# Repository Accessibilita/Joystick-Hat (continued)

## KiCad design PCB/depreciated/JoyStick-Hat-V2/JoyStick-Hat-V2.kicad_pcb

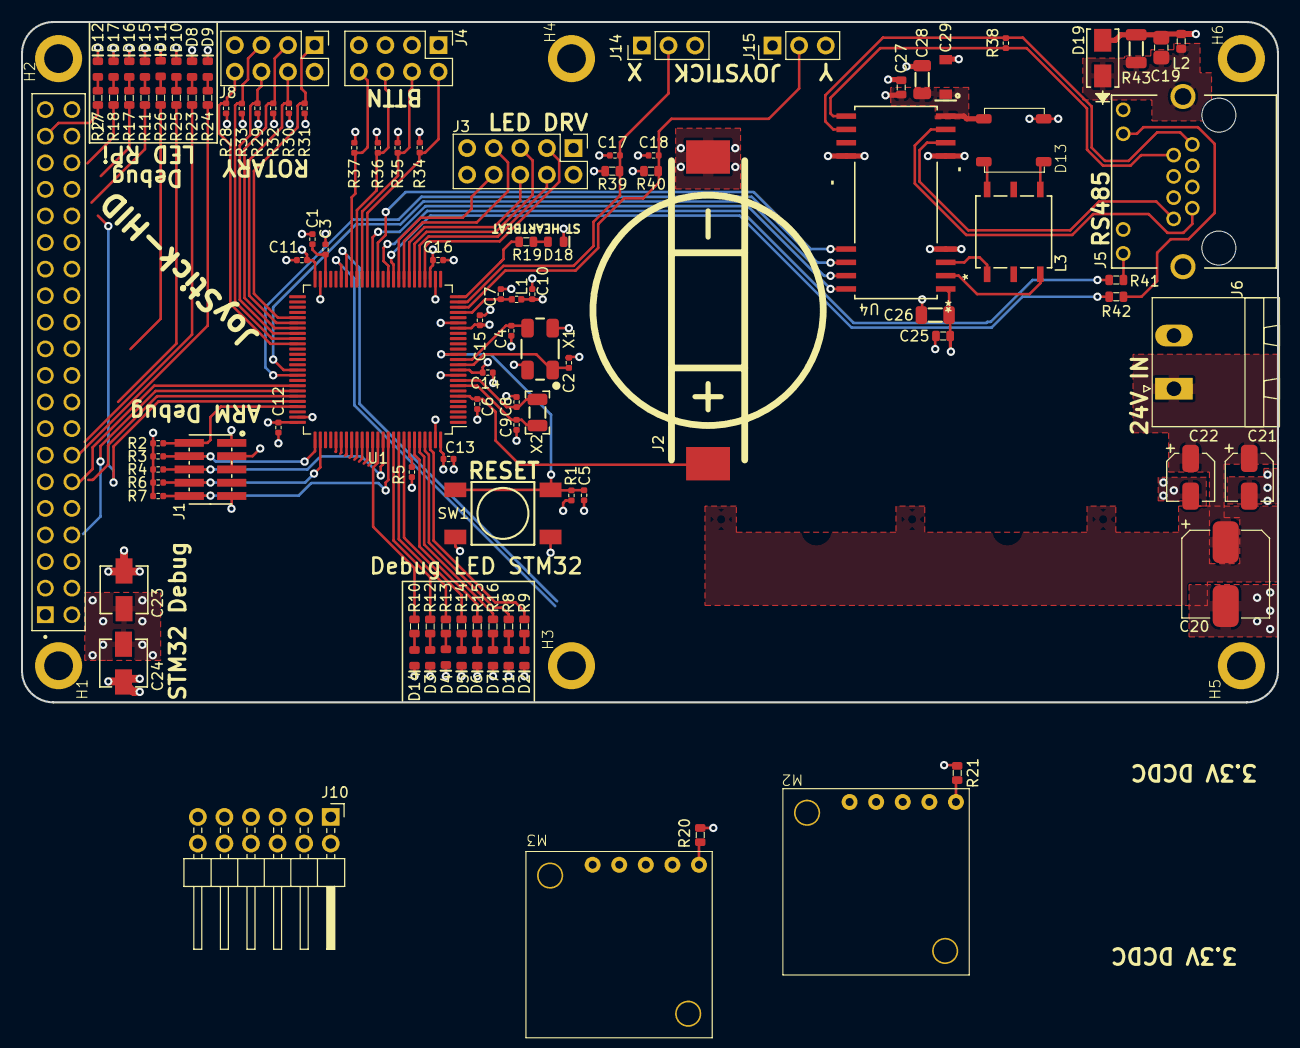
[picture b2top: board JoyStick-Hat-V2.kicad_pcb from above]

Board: 4 copper layers, 120.0 x 65.0 mm, 117 parts (0 on the bottom side), 104 nets.

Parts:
C1, C5, C6, C7, C10, C11, C12, C13, C14, C15, C16, C17, C18: C0402C104K9PACTU; R0402
C2, C4: GCM1555C1H180GA16D; C0402
C3: GRM155R60J475ME47D; C0402
C8, C9: CL05C090CB5NNNC; C0402
C19: C0805C103KCRACAUTO; C0805
C20: UUQ1H470MCL1GS; CP_Elec_8x10
C21: UUQ1H100MCL1GB; CP_Elec_4x5.3
C22: UUQ1H010MCL1GB; CP_Elec_4x5.3
C23, C24: UCM1C470MCL1GS
C25, C27: CL10B104JB8NNNC; C0603
C26, C28: CGA5L3X5R1V106K160AB; C1206
C29: C1206C105K3RACAUTO; D_SOD-123
D1, D2, D3, D4, D5, D6, D7, D14, D18: LTST-C194TBKT; LED0603
D8, D9, D10, D11, D12, D15, D16, D17: LTST-C194KGKT; LED0603
D13: LMB110S-TP
D19: SMAJ30CA
H1, H2, H3, H4, H5, H6: MountingHole_Pad; RPI_HAT_HOLE
J1: 20021121-00010C4LF
J2: BU2032SM-JJ-GTR
J3: Conn_02x05_Odd_Even; PinHeader_2x05_P2.54mm_Vertical
J4, J8: Conn_02x04_Odd_Even; PinHeader_2x04_P2.54mm_Vertical
J5: RJHSE-5381; AMPHENOL_RJHSE-5381
J6: 1757242; PhoenixContact_MSTBA-G_02x5.08mm_Angled
J7: Raspberry_Pi_2_3; SULLINS_PPPC202LFBN-RC_RPi5
J10: Conn_02x06_Odd_Even; PinHeader_2x06_P2.54mm_Horizontal
J14, J15: Conn_01x03_Pin; PinHeader_1x03_P2.54mm_Vertical
L1: BLM15HG601SN1D
L2: MI0603K300R-10
L3: Q4470-CL; SO6_Q4470-CL_C-SIZE_COC
M2: D24V22F5; D24V22F12
M3: D24V22F3; D24V22F12
R1, R2, R3, R4, R6, R7: RC0402FR-071KL; R0402
R5: RC0402FR-0710KL; R0402
R8, R9, R10, R11, R12, R13, R14, R15, R16, R17, R18, R19, R23, R24, R25, R26, R27, R41, R42: RC0603FR-07470RL; R0603
R20, R21: RC0603FR-072K2L; R0603
R28, R29, R30, R31, R32, R33, R34, R35, R36, R37: RC0402FR-072K2L; R0402
R38: AC0402FR-07120RL; R0402
R39, R40: RT0603BRD071ML; R0603
R43: RC1206FR-071ML; R1206
SW1: TL3301NF260QG
U1: STM32F446VETx; LQFP-100_14x14mm_P0.5mm
U4: MAX3535ECWI+T; 21-0145_W28M&plus_9_MXM
X1: ABM3B-8.000MHZ-B2-T; ABM3B8.000MHZB2T
X2: ABS07-32.768KHZ-9-T

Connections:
+3.3V: C10.1, C11.1, C12.1, C13.1, C14.1, C15.1, C16.1, C25.2, C26.2, J1.1, J3.1, J3.2, J14.3, J15.3, L1.1, M3.5 (VOUT), R1.1, R2.1, R3.1, R4.1, R6.1, R7.1, R20.2, R21.2, R28.2, R29.2, R30.2, R31.2, R32.2, R33.2, R34.2, R35.2, R36.2, R37.2, R39.2, R40.2, U1.11 (VDD), U1.19 (VDD), U1.28 (VDD), U1.50 (VDD), U1.75 (VDD), U1.100 (VDD), U4.1 (VCC1)
+5V: C23.1, C24.1, C27.2, C28.2, C29.2, D13.3, J7.2 (5V), J7.4 (5V), M2.5 (VOUT), U4.14 (VCC2)
+24V: C20.1, C21.1, C22.1, J6.1, M2.3 (VIN), M3.3 (VIN)
/JoyStick Interface/BUTTON1: J4.2, R34.1, U1.40 (PE9)
/JoyStick Interface/BUTTON2: J4.4, R35.1, U1.41 (PE10)
/JoyStick Interface/BUTTON3: J4.6, R36.1, U1.42 (PE11)
/JoyStick Interface/BUTTON4: J4.8, R37.1, U1.43 (PE12)
/JoyStick Interface/JOYSTICK_X: C17.1, J14.2, R39.1, U1.24 (PA1)
/JoyStick Interface/JOYSTICK_Y: C18.1, J15.2, R40.1, U1.23 (PA0)
/JoyStick Interface/ROTARY1_POLE1: J8.1, R31.1, U1.55 (PD8)
/JoyStick Interface/ROTARY1_POLE2: J8.3, R32.1, U1.57 (PD10)
/JoyStick Interface/ROTARY1_POLE3: J8.5, R33.1, U1.59 (PD12)
/JoyStick Interface/ROTARY2_POLE1: J8.8, R28.1, U1.60 (PD13)
/JoyStick Interface/ROTARY2_POLE2: J8.6, R29.1, U1.58 (PD11)
/JoyStick Interface/ROTARY2_POLE3: J8.4, R30.1, U1.56 (PD9)
/Power/3.3V_PG: M3.1 (PG), R20.1, U1.44 (PE13)
/Power/5V_PG: M2.1 (PG), R21.1, U1.45 (PE14)
/RPi_Interface/RPI_ST_UART_CTS: J7.36 (GPIO16), U1.71 (PA12)
/RPi_Interface/RPI_ST_UART_RTS: J7.11 (GPIO17), U1.70 (PA11)
/RPi_Interface/RPI_ST_UART_RX: J7.10 (GPIO15/RXD), U1.68 (PA9)
/RPi_Interface/RPI_ST_UART_TX: J7.8 (GPIO14/TXD), U1.69 (PA10)
/RS485 To Motor Controller Interface/A_RS485: J5.1, R38.1, U4.16 (A)
/RS485 To Motor Controller Interface/B_RS485: J5.2, R38.2, U4.15 (B)
/RS485 To Motor Controller Interface/RJ45_SHIELD: C19.1, D19.1, J5.S1, J5.S2, L2.1, R43.2
/RS485 To Motor Controller Interface/RS485_RXD: U1.39 (PE8), U4.28 (RO1)
/RS485 To Motor Controller Interface/RS485_RX_EN: U1.66 (PC9), U4.26 (DE)
/RS485 To Motor Controller Interface/RS485_RX_LED: R42.2, U1.35 (PB0)
/RS485 To Motor Controller Interface/RS485_TXD: U1.38 (PE7), U4.25 (DI)
/RS485 To Motor Controller Interface/RS485_TX_EN: U1.65 (PC8), U4.27 (RE)
/RS485 To Motor Controller Interface/RS485_TX_LED: R41.2, U1.36 (PB1)
/RS485 To Motor Controller Interface/Y_RS485: J5.7, U4.13 (Y)
/RS485 To Motor Controller Interface/Z_RS485: J5.8, U4.12 (Z)
/STM32F446RET6-MCU/LED_DRIVER_BLANK: J3.7, U1.33 (PC4)
/STM32F446RET6-MCU/LED_DRIVER_BLANK2: J3.5, U1.31 (PA6)
/STM32F446RET6-MCU/LED_DRIVER_MOSI: J3.6, U1.32 (PA7)
/STM32F446RET6-MCU/LED_DRIVER_SCLK: J3.4, U1.30 (PA5)
/STM32F446RET6-MCU/LED_DRIVER_XLAT: J3.3, U1.29 (PA4)
/STM32F446RET6-MCU/LED_DRIVER_XLAT2: J3.8, U1.34 (PC5)
/STM32F446RET6-MCU/NJTRST: J1.10, R7.2, U1.90 (PB4)
/STM32F446RET6-MCU/NRST: C5.1, R1.2, SW1.1, SW1.2, U1.14 (NRST)
/STM32F446RET6-MCU/OSC32_IN: C9.2, U1.8 (PC14), X2.2
/STM32F446RET6-MCU/OSC32_OUT: C8.2, U1.9 (PC15), X2.1
/STM32F446RET6-MCU/OSC_IN: C2.1, U1.12 (PH0), X1.1
/STM32F446RET6-MCU/OSC_OUT: C4.1, U1.13 (PH1), X1.3
/STM32F446RET6-MCU/PC10: J10.11, U1.78 (PC10)
/STM32F446RET6-MCU/PC11: J10.12, U1.79 (PC11)
/STM32F446RET6-MCU/PC12: J10.9, U1.80 (PC12)
/STM32F446RET6-MCU/PD0: J10.10, U1.81 (PD0)
/STM32F446RET6-MCU/PD1: J10.7, U1.82 (PD1)
/STM32F446RET6-MCU/PD2: J10.8, U1.83 (PD2)
/STM32F446RET6-MCU/PD3: J10.5, U1.84 (PD3)
/STM32F446RET6-MCU/PD4: J10.6, U1.85 (PD4)
/STM32F446RET6-MCU/PD5: J10.3, U1.86 (PD5)
/STM32F446RET6-MCU/PD6: J10.4, U1.87 (PD6)
/STM32F446RET6-MCU/SWCLK_TCK: J1.4, R3.2, U1.76 (PA14)
/STM32F446RET6-MCU/SWDIO_TMS: J1.2, R2.2, U1.72 (PA13)
/STM32F446RET6-MCU/SWO_TDI: J1.8, R6.2, U1.77 (PA15)
/STM32F446RET6-MCU/SWO_TDO: J1.6, R4.2, U1.89 (PB3)
/STM32F446RET6-MCU/VBAT: C6.1, J2.1 (+), U1.6 (VBAT)
/STM32F446RET6-MCU/VCAP1: C1.1, C3.1, U1.48 (VCAP_1)
/STM32F446RET6-MCU/VDDA: C7.1, L1.2, U1.22 (VDDA)
Earth: C27.1, C28.1, C29.1, D13.4, U4.11 (GND2), U4.18 (SLO)
GND: C1.2, C2.2, C3.2, C4.2, C5.2, C6.2, C7.2, C8.1, C9.1, C10.2, C11.2, C12.2, C13.2, C14.2, C15.2, C16.2, C17.2, C18.2, C19.2, C20.2, C21.2, C22.2, C23.2, C24.2, C25.1, C26.1, D1.2, D2.2, D3.2, D4.2, D5.2, D6.2, D7.2, D8.2, D9.2, D10.2, D11.2, D12.2, D14.2, D15.2, D16.2, D17.2, D18.2, D19.2, J1.3, J1.5, J1.9, J2.2 (-), J3.9, J3.10, J4.1, J4.3, J4.5, J4.7, J5.9, J5.11, J6.2, J7.6 (GND), J7.9 (GND), J7.14 (GND), J7.20 (GND), J7.25 (GND), J7.30 (GND), J7.34 (GND), J7.39 (GND), J8.2, J8.7, J10.1, J10.2, J14.1, J15.1, L2.2, M2.4 (GND), M3.4 (GND), R5.1, R43.1, SW1.3, SW1.4, U1.10 (VSS), U1.20 (VSSA), U1.27 (VSS), U1.49 (VSS), U1.74 (VSS), U1.99 (VSS), U4.4 (GND1), X1.2, X1.4
unnamed: D1.1, R8.2
unnamed: D2.1, R9.2
unnamed: D3.1, R12.2
unnamed: D4.1, R13.2
unnamed: D5.1, R14.2
unnamed: D6.1, R15.2
unnamed: D7.1, R16.2
unnamed: D8.1, R23.1
unnamed: D9.1, R24.1
unnamed: D10.1, R25.1
unnamed: D11.1, R26.1
unnamed: D12.1, R27.1
unnamed: D13.1, L3.4
unnamed: D13.2, L3.6
unnamed: D14.1, R10.2
unnamed: D15.1, R11.1
unnamed: D16.1, R17.1
unnamed: D17.1, R18.1
unnamed: D18.1, R19.2
unnamed: J5.10, R42.1
unnamed: J5.12, R41.1
unnamed: J7.35 (GPIO19/MISO1), R17.2
unnamed: J7.38 (GPIO20/MOSI1), R18.2
unnamed: J7.15 (GPIO22), R23.2
unnamed: J7.16 (GPIO23), R24.2
unnamed: J7.18 (GPIO24), R25.2
unnamed: J7.22 (GPIO25), R26.2
unnamed: J7.37 (GPIO26), R27.2
unnamed: J7.33 (PWM1/GPIO13), R11.2
unnamed: R5.2, U1.94 (BOOT0)
unnamed: R19.1, U1.25 (PA2)
unnamed: R12.1, U1.91 (PB5)
unnamed: R13.1, U1.92 (PB6)
unnamed: R14.1, U1.93 (PB7)
unnamed: R15.1, U1.95 (PB8)
unnamed: R16.1, U1.96 (PB9)
unnamed: R10.1, U1.88 (PD7)
unnamed: R8.1, U1.97 (PE0)
unnamed: R9.1, U1.98 (PE1)
unnamed: L3.3, U4.2 (ST1)
unnamed: L3.1, U4.3 (ST2)

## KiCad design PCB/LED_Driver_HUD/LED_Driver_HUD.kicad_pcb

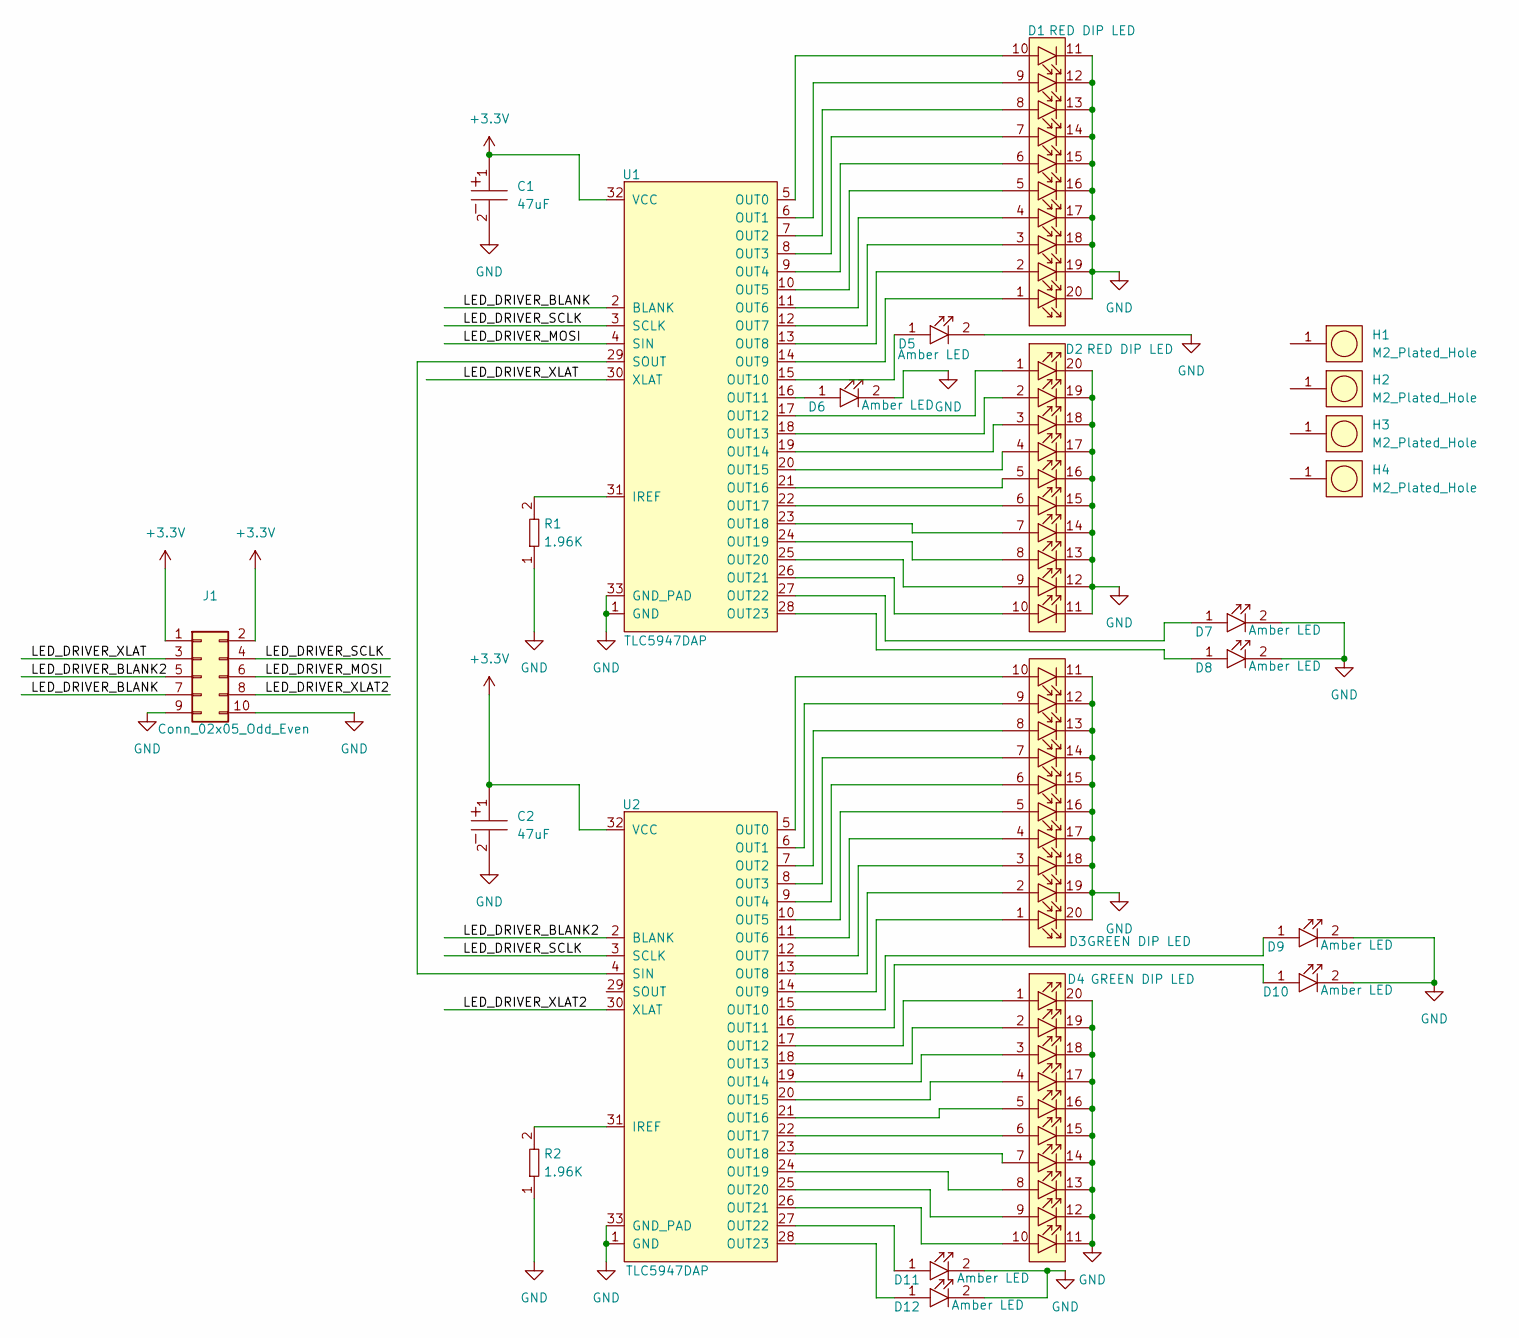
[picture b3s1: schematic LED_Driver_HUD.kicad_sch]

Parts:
C1, C2: UCM1C470MCL1GS; Tolerance 20%; Voltage 16V; MFR# UCM1C470MCL1GS
D1, D2: DC10EWA; DIP750W50P254L2540H825Q20; Tolerance *; Voltage 2V; MFR# DC10EWA
D3, D4: DC10GWA; DIP750W50P254L2540H825Q20; Tolerance *; Voltage 2.2V; MFR# DC10GWA
D5, D6, D7, D8, D9, D10, D11, D12: HLMP-1401; HLMP; Tolerance *; Voltage 2V; MFR# HLMP-1401
H1, H2, H3, H4: M2_Plated_Hole; M2_HOLE; Tolerance *; Voltage *; MFR# *
J1: Conn_02x05_Odd_Even; PinHeader_2x05_P2.54mm_Vertical
R1, R2: RC0805FR-071K96L; R0805; Tolerance 1%; Voltage N/A; MFR# RC0805FR-071K96L
U1, U2: TLC5947DAP; DAP32_4P36X4P11; Tolerance N/A; Voltage 3-5.5VDC; MFR# TLC5947DAP

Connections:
+3.3V: C1.1, C2.1, J1.1, J1.2, U1.32 (VCC), U2.32 (VCC)
/LED_DRIVER_BLANK: J1.7, U1.2 (BLANK)
/LED_DRIVER_BLANK2: J1.5, U2.2 (BLANK)
/LED_DRIVER_MOSI: J1.6, U1.4 (SIN)
/LED_DRIVER_SCLK: J1.4, U1.3 (SCLK), U2.3 (SCLK)
/LED_DRIVER_XLAT: J1.3, U1.30 (XLAT)
/LED_DRIVER_XLAT2: J1.8, U2.30 (XLAT)
GND: C1.2, C2.2, D1.11, D1.12, D1.13, D1.14, D1.15, D1.16, D1.17, D1.18, D1.19, D1.20, D2.11, D2.12, D2.13, D2.14, D2.15, D2.16, D2.17, D2.18, D2.19, D2.20, D3.11, D3.12, D3.13, D3.14, D3.15, D3.16, D3.17, D3.18, D3.19, D3.20, D4.11, D4.12, D4.13, D4.14, D4.15, D4.16, D4.17, D4.18, D4.19, D4.20, D5.2, D6.2, D7.2, D8.2, D9.2, D10.2, D11.2, D12.2, J1.9, J1.10, R1.1, R2.1, U1.1 (GND), U1.33 (GND_PAD), U2.1 (GND), U2.33 (GND_PAD)
unnamed: R1.2, U1.31 (IREF)
unnamed: D1.10, U1.5 (OUT0)
unnamed: D1.9, U1.6 (OUT1)
unnamed: D1.8, U1.7 (OUT2)
unnamed: D1.7, U1.8 (OUT3)
unnamed: D1.6, U1.9 (OUT4)
unnamed: D1.5, U1.10 (OUT5)
unnamed: D1.4, U1.11 (OUT6)
unnamed: D1.3, U1.12 (OUT7)
unnamed: D1.2, U1.13 (OUT8)
unnamed: D1.1, U1.14 (OUT9)
unnamed: D5.1, U1.15 (OUT10)
unnamed: D6.1, U1.16 (OUT11)
unnamed: D2.1, U1.17 (OUT12)
unnamed: D2.2, U1.18 (OUT13)
unnamed: D2.3, U1.19 (OUT14)
unnamed: D2.4, U1.20 (OUT15)
unnamed: D2.5, U1.21 (OUT16)
unnamed: D2.6, U1.22 (OUT17)
unnamed: D2.7, U1.23 (OUT18)
unnamed: D2.8, U1.24 (OUT19)
unnamed: D2.9, U1.25 (OUT20)
unnamed: D2.10, U1.26 (OUT21)
unnamed: D7.1, U1.27 (OUT22)
unnamed: D8.1, U1.28 (OUT23)
unnamed: U1.29 (SOUT), U2.4 (SIN)
unnamed: R2.2, U2.31 (IREF)
unnamed: D3.10, U2.5 (OUT0)
unnamed: D3.9, U2.6 (OUT1)
unnamed: D3.8, U2.7 (OUT2)
unnamed: D3.7, U2.8 (OUT3)
unnamed: D3.6, U2.9 (OUT4)
unnamed: D3.5, U2.10 (OUT5)
unnamed: D3.4, U2.11 (OUT6)
unnamed: D3.3, U2.12 (OUT7)
unnamed: D3.2, U2.13 (OUT8)
unnamed: D3.1, U2.14 (OUT9)
unnamed: D9.1, U2.15 (OUT10)
unnamed: D10.1, U2.16 (OUT11)
unnamed: D4.1, U2.17 (OUT12)
unnamed: D4.2, U2.18 (OUT13)
unnamed: D4.3, U2.19 (OUT14)
unnamed: D4.4, U2.20 (OUT15)
unnamed: D4.5, U2.21 (OUT16)
unnamed: D4.6, U2.22 (OUT17)
unnamed: D4.7, U2.23 (OUT18)
unnamed: D4.8, U2.24 (OUT19)
unnamed: D4.9, U2.25 (OUT20)
unnamed: D4.10, U2.26 (OUT21)
unnamed: D11.1, U2.27 (OUT22)
unnamed: D12.1, U2.28 (OUT23)

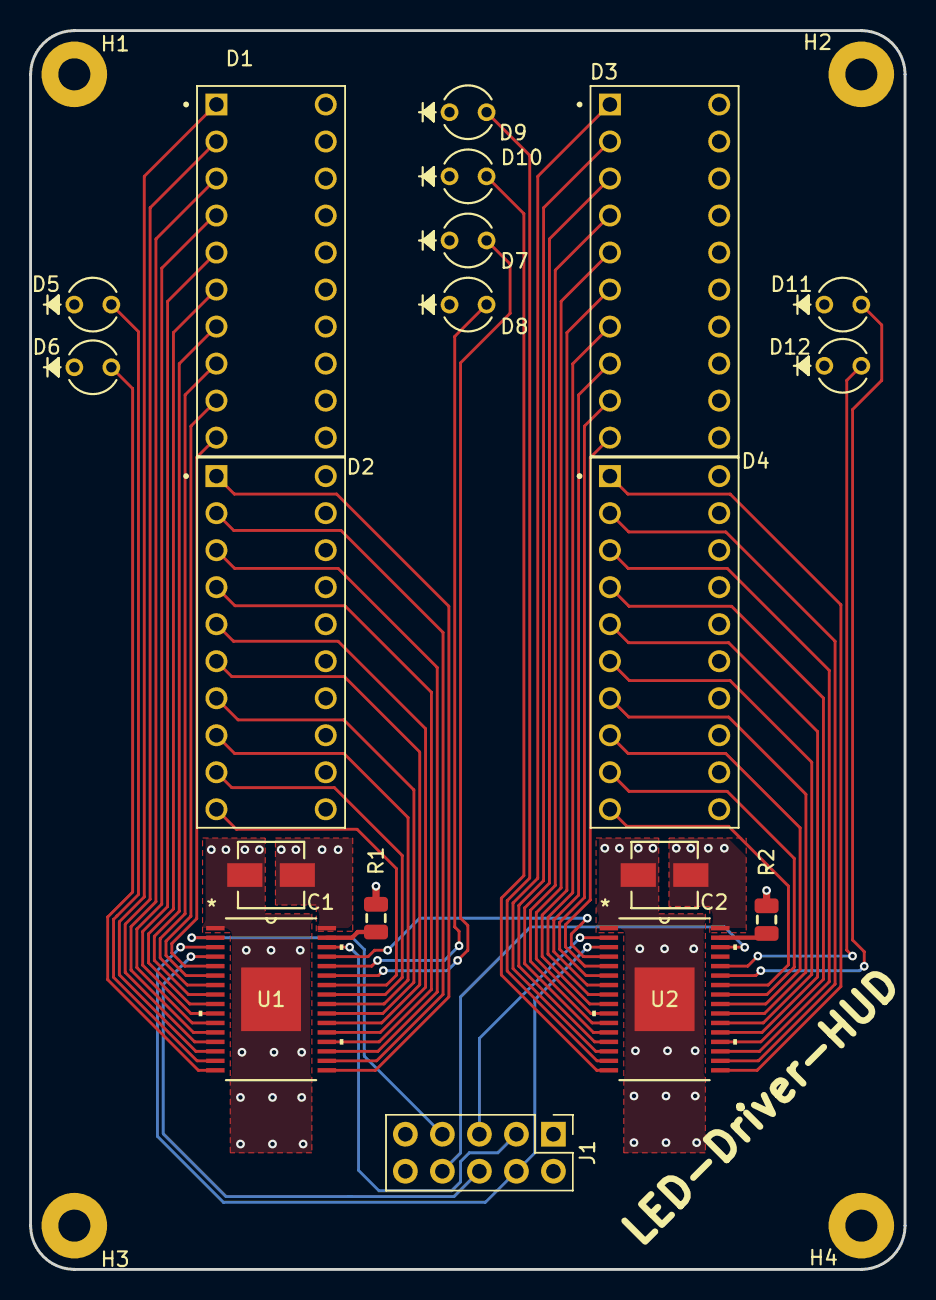
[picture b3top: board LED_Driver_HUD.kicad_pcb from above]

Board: 4 copper layers, 60.0 x 85.0 mm, 23 parts (0 on the bottom side), 59 nets.

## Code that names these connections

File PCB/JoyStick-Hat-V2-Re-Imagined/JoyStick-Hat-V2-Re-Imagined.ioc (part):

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Mcu.Name=STM32F446V(C-E)Tx
Mcu.Package=LQFP100
Mcu.UserName=STM32F446VETx
PA0-WKUP.Signal=ADCx_IN0
PA1.Signal=ADCx_IN1
PA10.Mode=Asynchronous
PA10.Signal=USART1_RX
PA11.Mode=CTS_RTS
PA11.Signal=USART1_CTS
PA12.Mode=CTS_RTS
PA12.Signal=USART1_RTS
PA2.Signal=ADCx_IN2
PA3.Signal=ADCx_IN3
PA4.Signal=ADCx_IN4
PA5.Mode=Full_Duplex_Master
PA5.Signal=SPI1_SCK
PA6.Mode=Full_Duplex_Master
PA6.Signal=SPI1_MISO
PA7.Mode=Full_Duplex_Master
PA7.Signal=SPI1_MOSI
PA9.Mode=Asynchronous
PA9.Signal=USART1_TX
PB7.Signal=GPIO_Output
PB8.Signal=GPIO_Output
PB9.Signal=GPIO_Output
PC10.Signal=GPIO_Input
PC11.Signal=GPIO_Input
PC12.Signal=GPIO_Input
PC13.Signal=GPIO_Input
PC14-OSC32_IN.Signal=RCC_OSC32_IN
PC15-OSC32_OUT.Signal=RCC_OSC32_OUT
PC4.Signal=GPIO_Output
PC5.Signal=GPIO_Output
PC6.Signal=GPIO_Output
PC7.Signal=GPIO_Output
PC8.Mode=CTS_RTS
PC8.Signal=UART5_RTS
PC9.Mode=CTS_RTS
PC9.Signal=UART5_CTS
PD0.Signal=GPIO_Output
PD1.Signal=GPIO_Output
PD10.Signal=GPIO_Input
PD11.Signal=GPIO_Input
PD12.Signal=GPIO_Input
PD13.Signal=GPIO_Input
PD14.Signal=FMPI2C1_SCL
PD15.Signal=FMPI2C1_SDA
PD2.Signal=GPIO_Output
PD3.Mode=CTS_RTS
PD3.Signal=USART2_CTS
PD4.Mode=CTS_RTS
PD4.Signal=USART2_RTS
PD5.Mode=Asynchronous
PD5.Signal=USART2_TX
PD6.Mode=Asynchronous
PD6.Signal=USART2_RX
PD8.Signal=GPIO_Input
PD9.Signal=GPIO_Input
PE10.Signal=GPIO_Input
PE11.Signal=GPIO_Input
PE12.Signal=GPIO_Input
PE13.Signal=GPIO_Input
PE2.Signal=GPIO_Output
PE3.Signal=GPIO_Output
PE4.Signal=GPIO_Output
PE5.Signal=GPIO_Output
PE6.Signal=GPIO_Output
PE7.Mode=Asynchronous
PE7.Signal=UART5_RX
PE8.Mode=Asynchronous
PE8.Signal=UART5_TX
PE9.Signal=GPIO_Input
PH0-OSC_IN.Signal=RCC_OSC_IN
PH1-OSC_OUT.Signal=RCC_OSC_OUT
board=custom

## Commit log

2023-08-24 Schematic and Libraries
    Started the schematic and started making footprints and symbols for the new components needed in the design.
2023-09-22 MCU
    MCU schematic added and 90% complete
2023-09-27 Power and LED Driver
    Power Supply Schematic sketched out using Pololu power regulator modules to hasten design. LED drivers replaced with ones that have 24 ouputs so we can use 20 unit bar graph LEDs and have 8 extra cha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
2023-10-04 LED drivers and Joystick
    Finished LED driver scheamtics, corrected some problems with symbols. added conenctors for joystick and buttons, connected RPI pins to MCU
2023-10-04 Sheet Conenctivity and RS485
    Added more sheet entries throughuot the project connecting different subsystems to the main MCU schematic. Also added new sheet for the RS485 interface for communicating with the motor control board.
2023-10-20 Schematic Progress
    Made progress with schematic and corrected designator letters with connectors to match the built in paradigm of using J instead of T. T will not be used to referencing transformers instead of connect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
2023-11-12 Schematic Complete
    Schematic completed. Moved to 100 pin version of STM32 MCU for more connectivity and better muxing of internal peripherals with pins.
2023-11-12 PCB Created
    Schematic and footprint bugs knocked out PCB created and parts imported into board.
2023-11-12 LEDs and Additional connectors
    Added heartbeat and diagnostic LEDs to STM32 and RPi3 schematics so we can directly flash them for debug purposes. Added a connector for serial port diagnostics on STM32. Added rotary switch interfac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
2023-11-12 CubeMX Update
    Updated CubeMX project to reflect additional serial port in use.
2023-11-18 Board Shape and Layout
    Board Shape added and layout started !
2023-11-21 Design Rules, Component Placement. Features Dropped
    Added design rules for OSHPark.com to PCB, Most components placed roughly for whole board more to follow and more tweaks,. Features were dropped/rearanged. USB for STM32 dropped as its not necessary.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
2023-12-12 Board Tweaks and progress
    Made progress with baord. Adjusted the position of RPi header to be correct and absolute. Changed location of regulator modules and power input capacitors. Added 3D models missing from the larger com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
2023-12-21 Board Routing
    Connectors swapped around and board route started
2024-01-10 Board Progress
    Board route nearly complete, internal power plane topologys witched up to run 5Vs as plane. Reset buttom moved. Next: add more LEDs and breakout more STM32 pins for development purposes.
2024-01-11 PCB First Pass Complete
    First complete pass at PCB finished. Added more debug LEDs for both STM32 and RPi, 8 totaly so binary data can be outputted as a byte etc, that way we can have debug codes. Added heartbeat LED to STM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
2024-01-23 BOM
    BOM Exported and converted to LibreOffice format
2024-01-25 Fab Estimations
    Estimating cost of fabrication
2024-03-12 James Fixes and 3D models
    Added all the changes that James suggested to the design and then added 3D models to the board for mechanical design purposes. Generated 3D renders of the board and added them to new directory called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
2024-03-12 Update README.md
    Updated readme with quick specs for the hat
2024-03-12 LED_Driver_HUD and 2D render
    Added new project for LED Driver HUD board, a daughter board that drives LEDs for displaying battery power level and wheel chair set speed. Added 2D render of Joystick-HID Hat
2024-03-12 Update README.md
    Added images to Readme from img folder
2024-03-12 Block Diagram
    Block diagram from Hackaday page added.
2024-03-12 Update README.md
    added block diagram !
2024-04-27 RJ45
    Replaced RJ45 connector, original one had magnetics, those are not needed for RS485 and would have caused problems. Hooked up coms LEDs on RJ45 connector to MCU for debugging and displaying coms acti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
2024-04-27 Power Input Moved
    Power input connector moved to be flush with board!
2024-05-21 Board Tweaks
    Copper pour specifications adjusted and repoured. DRC errors are caused by silkscreen , this happened when updating from KiCAD 7 to 8, still investigating it.
2024-05-23 BOM
    Bom saved in libreoffice format
2024-07-08 Silkscreen Tweaks
    Added lots of labels to silkscreen and moved some traces
2024-07-09 Connectors Moved, Labels Added, and New Images
    Moved connectors around so labels can be fit on the bottom of PCB, labels added to bottom of PCB. New images exported !
2024-07-11 LED Driver HUD
    Finished PCB design of LED Driver HUD PCB, First pass of route DRC full pass. Next update adding additional LEDs for additional display functions
2024-07-11 LED HUD Complete
    Added Additional indicator LEDs to LED HUD board. Full DRC pass.
2024-07-23 Board ordered
    Board ordered
2024-07-24 3D Model
    3D Model Generated
2024-08-03 Switching Workstations
    syncing to switch to mobile workstation
2024-08-12 V2
    Started version 2 design and reworking
2024-08-12 Assembly notes
    Started notes on assembly
2024-08-12 Joystick Hat V2 Progress
    Powersupply section laid out on V2 of JoyStick Hat PCB
2024-08-17 Assmbly Notes
    More added to assembly notes and IDE datasheet
2024-08-22 V2
    Lots of progress made on version two of JoyStick Hat but the RPi 5 is going to be elimintated and an additional RS485 port added.
2024-09-04 RPi Removed
    Removed RPi from circuit added 20 pin JTAG schematic and PCB stil WIP
2024-09-17 Assmbly notes
    Assembly notes updated after debug interface hardware bug resolved.
2024-09-25 V2
    V2 Schematic and Debug connector on PCB corrected
2024-09-30 V2 PCB First PAss Complete
    First pass of V2 PCB Completeded !
2024-09-30 Schematic Tweak
    Making MCU page more readable
2024-11-02 V2 Tweaks
    More Tweaks to the completed V2 design. 3D renders of V2 design produced and added to img folder for documentation update coming in the next commit. Photos of prototype also added to img folder for d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
2024-11-02 Update README.md
    First update to readme. Added documentation for V 0.2a and the assembly of prototype of 0.1a. Diagrams for 0.2a need to be added.
2024-11-02 Images
    Removed irrelevant image, added 2D render of version 0.2a of JoyStick-HID !
2024-11-02 Diagram Fix
    Title in Diagram was incorrect.
2024-11-02 Update README.md
    Updated diagram for version 0.2a, added 2D render of JoyStick-HID version 0.2a and added firmware link to assembly doc
2024-11-02 Update README.md
    Project description to update major changes
2024-11-06 Schematic and board tweaks
    tweaks to analog power section of MCU
2024-11-23 Daisy Chaining
    Modified RS485 circuit with dual port connector for daisy chaining systems on the wheel chair !
2024-12-04 Version 2 DRC and BOM
    Joystick-HID V2 Reimagined design completed and ready for fab !! BOM generated and clean.
2024-12-17 Fab Fixes
    Fixing for Frabrication, DRC cleared by pending external review subject to change.
2024-12-18 STM32 Exp
    Removed 5V regulator, corrected RS485 schematic, added more expansion to STM32 since we had space.
2024-12-18 Organization
    Organized the repo
2024-12-20 RS485 Circuit Fixes, STM32 Expansion
    Fixe RS485 circuit errors, changed PCB topology for RS485. Added STM32 expansion IO in place of 5V Regulator.
2024-12-27 Power plan
    Power plane shape adjusted
2025-01-01 Documentation
    Updated renders
2025-01-09 3D Model
    3D model generated and added to the project.
2025-01-09 Schematic cleanup and new IO MAp
    Unused sheet pins deleted from main page, and STM32CubeMX IO map for JoyStick-HID V2 added.
2025-01-13 Front Page Cleanup
    Removed old sheet pins and wires from hierachal page since 12v and 5v are no longer in the system.
2025-03-11 Silkscreen
    Bottom Silkscreen edit.
2025-03-11 GitIgnore
    changes to gitignore
2025-03-11 Cleanup
